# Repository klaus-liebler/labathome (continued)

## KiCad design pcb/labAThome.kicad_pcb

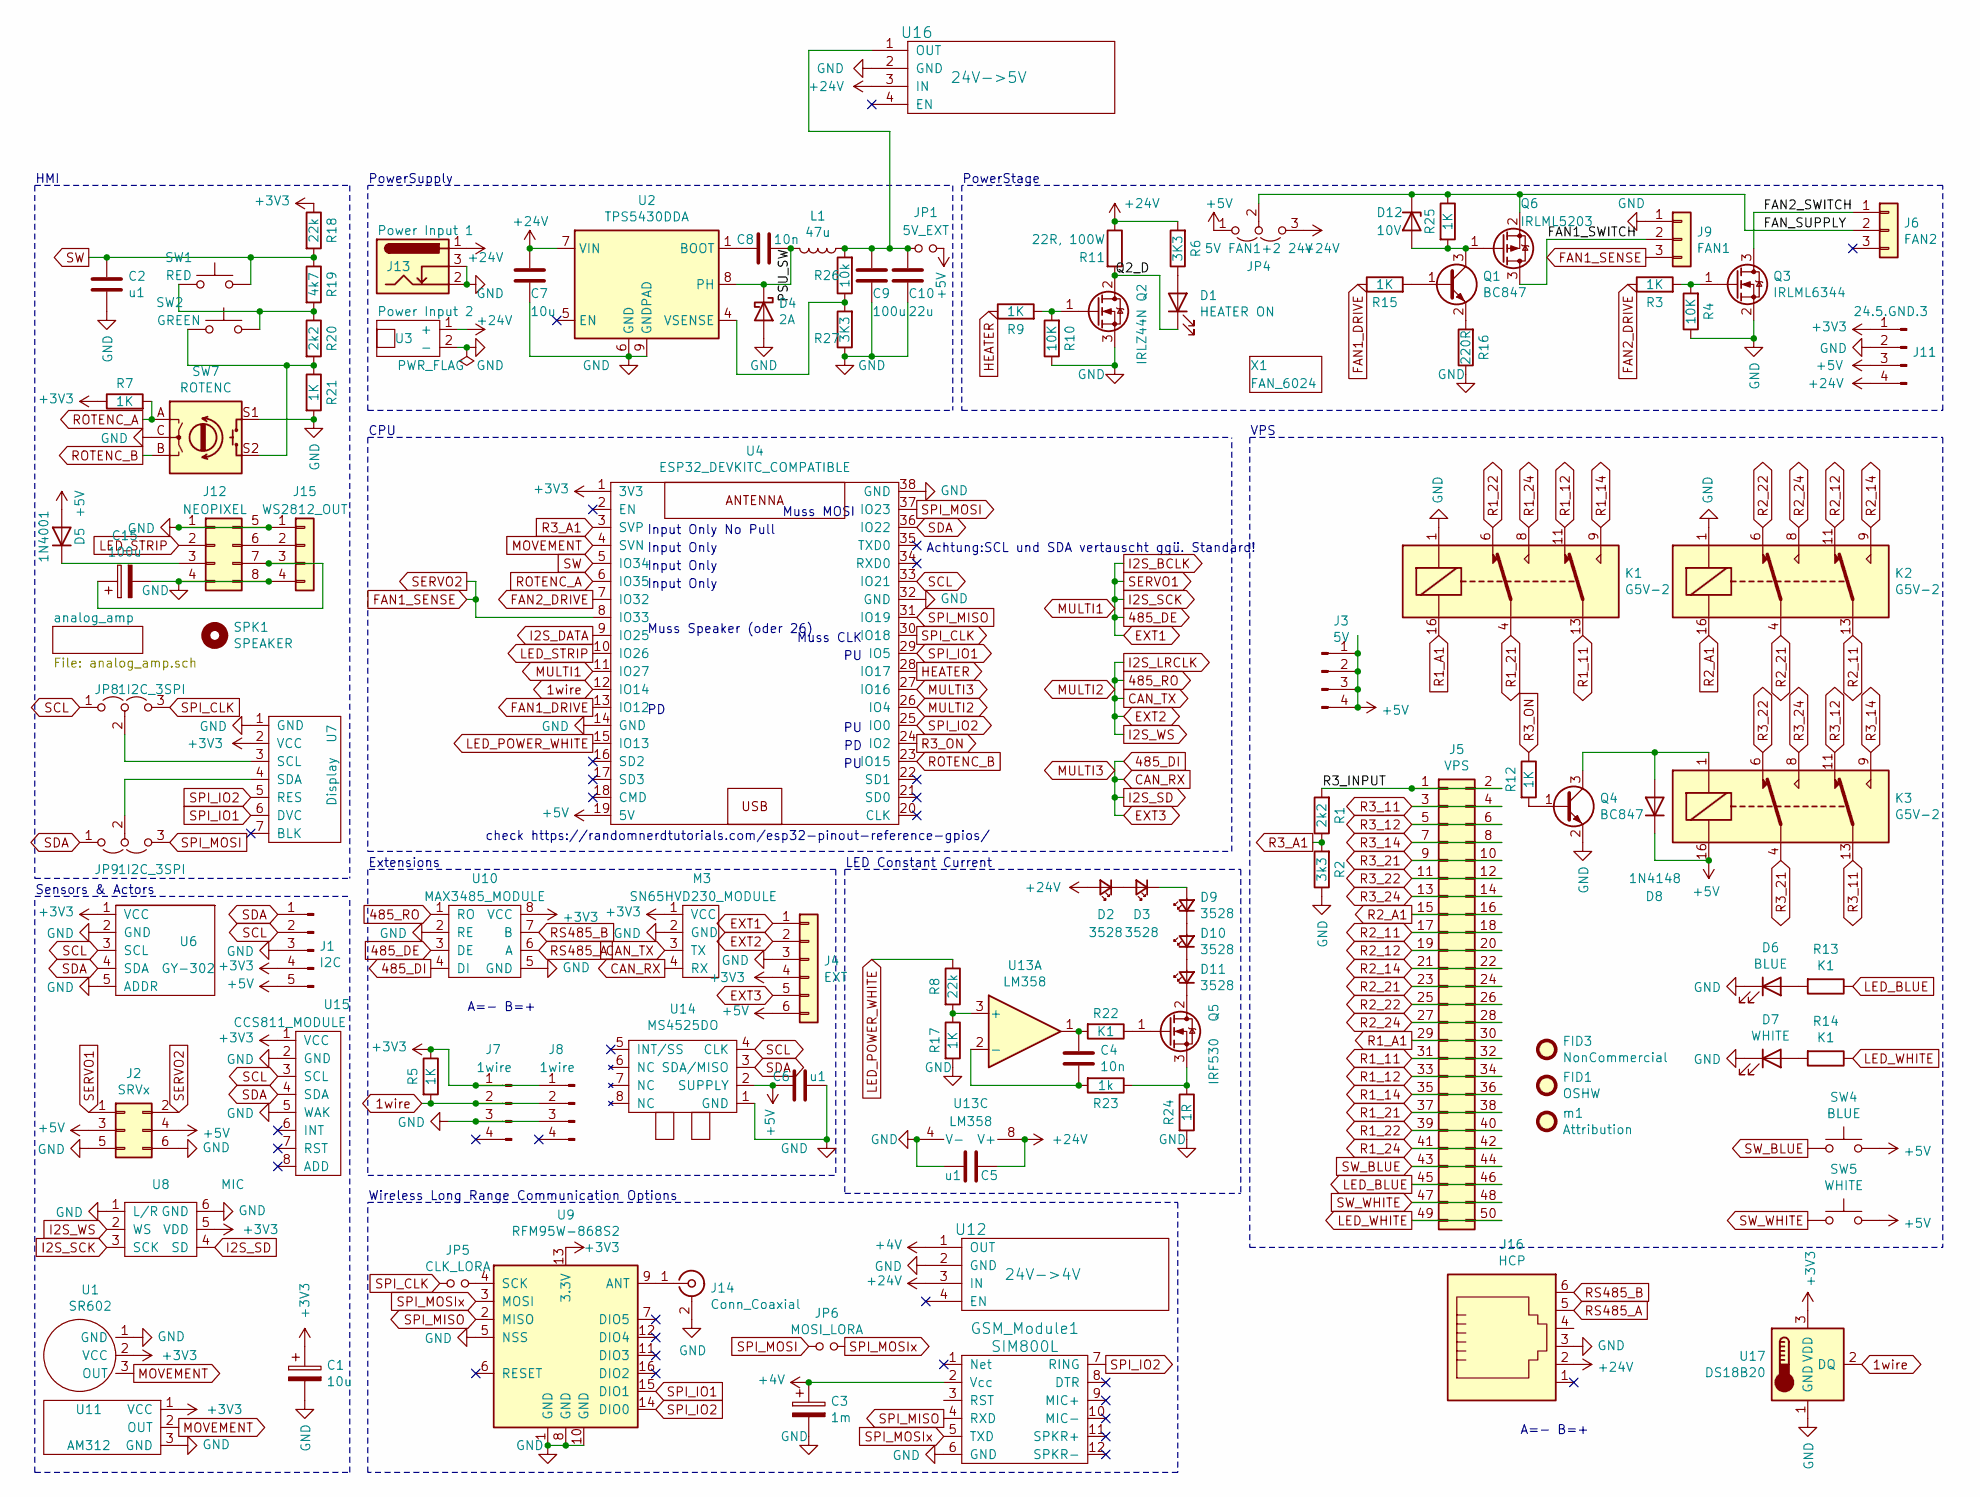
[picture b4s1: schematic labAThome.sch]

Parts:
C1: 10u; CP_EIA-3216-18_Kemet-A_Pad1.58x1.35mm_HandSolder
C2, C5, C6: u1; C_1206_3216Metric_Pad1.42x1.75mm_HandSolder
C3: 1m; CP_EIA-7360-38_Kemet-E_Pad2.25x4.25mm_HandSolder
C4: 10n; C_1206_3216Metric_Pad1.42x1.75mm_HandSolder
C7: 10u; C_1206_3216Metric_Pad1.33x1.80mm_HandSolder
C8: 10n; C_1206_3216Metric_Pad1.33x1.80mm_HandSolder
C9: 100u; C_1206_3216Metric_Pad1.33x1.80mm_HandSolder
C10: 22u; C_1206_3216Metric_Pad1.33x1.80mm_HandSolder
C15: 100u; CP_Elec_6.3x7.7_handsolder
D1: HEATER ON; LED_D5.0mm
D2, D3, D9, D10, D11: 3528; LED_PLCC_2835_Handsoldering
D4: 2A; do214aa_handsolder
D5: 1N4001; D_SMA_Handsoldering
D6: BLUE; LED_D5.0mm
D7: WHITE; LED_D5.0mm
D8: 1N4148; D_SMA_Handsoldering
D12: 10V; D_SMA_Handsoldering
FID1: OSHW; OSHW-Logo_5.7x6mm_SilkScreen
FID3: NonCommercial; Symbol_CC-Noncommercial_CopperTop_Small
GSM_Module1: SIM800L
J1: I2C; JST_XH_B5B-XH-AM_1x05_P2.50mm_Vertical
J2: SRVx; PinHeader_2x03_P2.54mm_Vertical
J3: 5V; PinHeader_1x04_P2.54mm_Vertical
J4: EXT; JST_XH_B6B-XH-A_1x06_P2.50mm_Vertical
J5: VPS; PinHeader_2x25_P2.54mm_Vertical
J6: FAN2; FanPinHeader_1x03_P2.54mm_Vertical
J7, J8: 1wire; JST_XH_B4B-XH-A_1x04_P2.50mm_Vertical
J9: FAN1; FanPinHeader_1x03_P2.54mm_Vertical
J11: 24.5.GND.3; JST_XH_B4B-XH-A_1x04_P2.50mm_Vertical
J12: NEOPIXEL; NEOPIXEL_STICK
J13: Power Input 1; BarrelJack_Horizontal
J14: Conn_Coaxial; SMA_Samtec_SMA-J-P-X-ST-EM1_EdgeMount
J15: WS2812_OUT; PinHeader_1x04_P2.54mm_Vertical
J16: HCP; WR_MJ_Modular_Jack_Vertical_Plastic_6P6C
JP1: 5V_EXT; PinHeader_1x02_P2.54mm_Vertical
JP4: 5V FAN1+2 24V; PinSocket_1x03_P2.54mm_Vertical
JP5: CLK_LORA; SolderJumper-2_P1.3mm_Open_RoundedPad1.0x1.5mm
JP6: MOSI_LORA; SolderJumper-2_P1.3mm_Open_RoundedPad1.0x1.5mm
JP8, JP9: 1I2C_3SPI; SolderJumper-3_P1.3mm_Open_RoundedPad1.0x1.5mm_NumberLabels
K1, K2, K3: G5V-2; Relay_DPDT_Omron_G5V-2
L1: 47u; Inductor_CD104_handsolder
M3: SN65HVD230_MODULE
Q1, Q4: BC847; SOT-23_Handsoldering
Q2: IRLZ44N; TO-220-3_Horizontal_TabDown
Q3: IRLML6344; SOT-23_Handsoldering
Q5: IRF530; TO-220-3_Horizontal_TabDown
Q6: IRLML5203; SOT-23_Handsoldering
R1, R20: 2k2; R_1206_3216Metric_Pad1.42x1.75mm_HandSolder
R2: 3k3; R_1206_3216Metric_Pad1.42x1.75mm_HandSolder
R3, R5, R7, R9, R12, R15, R17, R21: 1K; R_1206_3216Metric_Pad1.42x1.75mm_HandSolder
R4, R10: 10K; R_1206_3216Metric_Pad1.42x1.75mm_HandSolder
R6: 3K3; R_1206_3216Metric_Pad1.42x1.75mm_HandSolder
R8, R18: 22k; R_1206_3216Metric_Pad1.42x1.75mm_HandSolder
R11: 22R, 100W; Resistor_100W
R13, R14, R22: K1; R_1206_3216Metric_Pad1.42x1.75mm_HandSolder
R16: 220R; R_1206_3216Metric_Pad1.42x1.75mm_HandSolder
R19: 4k7; R_1206_3216Metric_Pad1.42x1.75mm_HandSolder
R23: 1k; R_1206_3216Metric_Pad1.42x1.75mm_HandSolder
R24: 1R; R_1206_3216Metric_Pad1.42x1.75mm_HandSolder
R25: 1K; R_1206_3216Metric_Pad1.30x1.75mm_HandSolder
R26: 10k; R_1206_3216Metric_Pad1.30x1.75mm_HandSolder
R27: 3K3; R_1206_3216Metric_Pad1.30x1.75mm_HandSolder
SPK1: SPEAKER; SPEAKER_2415
SW1: RED; Button_12mm_ANCHOR_CENTER
SW2: GREEN; Button_12mm_ANCHOR_CENTER
SW4: BLUE; Button_12mm_ANCHOR_CENTER
SW5: WHITE; Button_12mm_ANCHOR_CENTER
SW7: ROTENC; RotaryEncoder_Alps_EC11E-Switch_Vertical_H20mm
U1: SR602; PIR_Sensor_SR602
U2: TPS5430DDA; SOIC-8_3.9x4.9mm_Pitch1.27mm_pad_handsolder
U3: Power Input 2; PDC004_Module
U4: ESP32_DEVKITC_COMPATIBLE
U6: GY-302
U7: Display; IPS_240_240
U8: MIC; INMP441_Module
U9: RFM95W-868S2; HOPERF_RFM9XW_SMD
U10: MAX3485_MODULE
U11: AM312
U12: 24V->4V; MODULE_STEPDOWN
U13: LM358; SOIC-8_3.9x4.9mm_Pitch1.27mm_handsolder
U14: MS4525DO
U15: CCS811_MODULE
U16: 24V->5V; MODULE_STEPDOWN
U17: DS18B20; TO-92_Inline
X1: FAN_6024
m1: Attribution; Symbol_CC-Attribution_CopperTop_Small

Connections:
1wire: J7.2, J8.2, R5.2, U4.12 (IO14), U17.2 (DQ)
485_DE: J2.1, J4.1, U4.11 (IO27), U8.3 (SCK), U10.3 (DE)
485_DI: J4.5, M3.4 (RX), U4.27 (IO16), U8.4 (SD), U10.4 (DI)
485_RO: J4.2, M3.3 (TX), U4.26 (IO4), U8.2 (WS), U10.1 (RO)
+3V3: C1.1, J1.4, J4.4, J7.1, J8.1, J11.1, M3.1 (VCC), R5.1, R7.1, R18.1, U1.2 (VCC), U4.1 (3V3), U6.1 (VCC), U7.2 (VCC), U8.5 (VDD), U9.13 (3.3V), U10.8 (VCC), U11.1 (VCC), U15.1 (VCC), U17.3 (VDD); also elsewhere on the board
+4V: C3.1, GSM_Module1.2 (Vcc), U12.1 (OUT)
+5V: C6.1, D5.2 (A), D8.1 (K), J1.5, J2.3, J2.4, J3.1, J3.2, J3.3, J3.4, J4.6, J11.3, JP1.1, JP4.1 (A), K3.16, SW4.2, SW5.2, U4.19 (5V), U14.2 (SUPPLY); also elsewhere on the board
+24V: C5.1, C7.1, D2.2 (A), J11.4, J13.1, J16.2, JP4.3 (B), R6.2, R11.1, U2.7 (VIN), U3.1 (+), U12.3 (IN), U13.8 (V+), U16.3 (IN)
/FAN1_SWITCH: J9.2, Q6.3 (D)
/FAN2_SWITCH: J6.1, Q3.3 (D)
/FAN_SUPPLY: D12.1 (K), J6.2, JP4.2 (C), Q6.2 (S), R25.1
/PSU_SW: C8.2, D4.1 (K), L1.2, U2.8 (PH)
/Q2_D: D1.1 (K), Q2.2 (D), R11.2
/R3_INPUT: J5.1, J5.2, R1.2
FAN1_DRIVE: R15.1, U4.13 (IO12)
FAN1_SENSE: J2.2, J9.3, U4.8 (IO33)
FAN2_DRIVE: R3.1, U4.7 (IO32)
GND: C1.2, C2.2, C3.2, C5.2, C6.2, C7.2, C9.2, C10.2, C15.2, D4.2 (A), D6.1 (K), D7.1 (K), GSM_Module1.6 (GND), J1.3, J2.5, J2.6, J4.3, J7.3, J8.3, J9.1, J11.2, J12.1, J12.4, J12.5, J12.8, J13.2, J13.3, J14.2 (Ext), J15.1, J15.4, J16.3, K1.1, K2.1, M3.2 (GND), Q2.3 (S), Q3.2 (S), Q4.2 (E), R2.1, R4.1, R10.1, R16.1, R17.2, R21.2, R24.2, R27.1, SW7.C, SW7.S1, U1.1 (GND), U2.6 (GND), U2.9 (GNDPAD), U3.2 (-), U4.14 (GND), U4.32 (GND), U4.38 (GND), U6.2 (GND), U6.5 (ADDR), U7.1 (GND), U8.1 (L/R), U8.6 (GND), U9.1 (GND), U9.5 (NSS), U9.8 (GND), U9.10 (GND), U10.2 (RE), U10.5 (GND), U11.3 (GND), U12.2 (GND), U13.4 (V-), U14.1 (GND), U15.2 (GND), U15.5 (WAK), U16.2 (GND), U17.1 (GND); also elsewhere on the board
HEATER: R9.1, U4.28 (IO17)
I2S_DATA: U4.9 (IO25); also elsewhere on the board
LED_BLUE: J5.45, J5.46, R13.1
LED_POWER_WHITE: R8.1, U4.15 (IO13)
LED_STRIP: J12.2, U4.10 (IO26)
LED_WHITE: J5.49, J5.50, R14.1
MOVEMENT: U1.3 (OUT), U4.4 (SVN), U11.2 (OUT)
unnamed: C4.1, R22.2, U13.1
unnamed: C4.2, R23.2, U13.2 (-)
unnamed: C8.1, U2.1 (BOOT)
unnamed: C9.1, C10.1, JP1.2, L1.1, R26.2, U16.1 (OUT)
unnamed: C15.1, J12.7, J15.3
unnamed: D1.2 (A), R6.1
unnamed: D2.1 (K), D3.2 (A)
unnamed: D3.1 (K), D9.2 (A)
unnamed: D5.1 (K), J12.3
unnamed: D6.2 (A), R13.2
unnamed: D7.2 (A), R14.2
unnamed: D8.2 (A), K3.1, Q4.3 (C)
unnamed: D10.1 (K), D11.2 (A)
unnamed: D9.1 (K), D10.2 (A)
unnamed: D11.1 (K), Q5.2 (D)
unnamed: D12.2 (A), Q1.3 (C), Q6.1 (G), R25.2
unnamed: J12.6, J15.2
unnamed: J14.1 (In), U9.9 (ANT)
unnamed: JP5.2, U9.4 (SCK)
unnamed: JP8.2 (C), U7.3 (SCL)
unnamed: JP9.2 (C), U7.4 (SDA)
unnamed: Q1.1 (B), R15.2
unnamed: Q1.2 (E), R16.2
unnamed: Q2.1 (G), R9.2, R10.2
unnamed: Q3.1 (G), R3.2, R4.2
unnamed: Q4.1 (B), R12.2
unnamed: Q5.1 (G), R22.1
unnamed: Q5.3 (S), R23.1, R24.1
unnamed: R8.2, R17.1, U13.3 (+)
unnamed: R19.2, R20.1, SW1.2, SW2.2
unnamed: R20.2, R21.1, SW2.1, SW7.S2
unnamed: R26.1, R27.2, U2.4 (VSENSE)
R1_11: J5.31, J5.32, K1.13
R1_12: J5.33, J5.34, K1.11
R1_14: J5.35, J5.36, K1.9
R1_21: J5.37, J5.38, K1.4
R1_22: J5.39, J5.40, K1.6
R1_24: J5.41, J5.42, K1.8
R1_A1: J5.29, J5.30, K1.16
R2_11: J5.17, J5.18, K2.13
R2_12: J5.19, J5.20, K2.11
R2_14: J5.21, J5.22, K2.9
R2_21: J5.23, J5.24, K2.4
R2_22: J5.25, J5.26, K2.6
R2_24: J5.27, J5.28, K2.8
R2_A1: J5.15, J5.16, K2.16
R3_11: J5.3, J5.4, K3.13
R3_12: J5.5, J5.6, K3.11
R3_14: J5.7, J5.8, K3.9
R3_21: J5.9, J5.10, K3.4
R3_22: J5.11, J5.12, K3.6
R3_24: J5.13, J5.14, K3.8
R3_A1: R1.1, R2.2, U4.3 (SVP)
R3_ON: R12.1, U4.24 (IO2)
ROTENC_A: R7.2, SW7.A, U4.6 (IO35)
ROTENC_B: SW7.B, U4.23 (IO15)
RS485_A: J16.5, U10.6 (A)
RS485_B: J16.6, U10.7 (B)
SCL: J1.2, JP8.1 (A), U4.33 (IO21), U6.3 (SCL), U14.4 (CLK), U15.3 (SCL)
SDA: J1.1, JP9.1 (A), U4.36 (IO22), U6.4 (SDA), U14.3 (SDA/MISO), U15.4 (SDA)
SPI_CLK: JP5.1, JP8.3 (B), U4.30 (IO18)
SPI_IO1: U4.29 (IO5), U7.6 (DVC), U9.15 (DIO1)
SPI_IO2: GSM_Module1.7 (RING), U4.25 (IO0), U7.5 (RES), U9.14 (DIO0)
SPI_MISO: GSM_Module1.4 (RXD), U4.31 (IO19), U9.2 (MISO)
SPI_MOSI: JP6.1, JP9.3 (B), U4.37 (IO23)
SPI_MOSIx: GSM_Module1.5 (TXD), JP6.2, U9.3 (MOSI)
SW: C2.1, R18.2, R19.1, SW1.1, U4.5 (IO34)
SW_BLUE: J5.43, J5.44, SW4.1
SW_WHITE: J5.47, J5.48, SW5.1

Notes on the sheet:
PowerStage
HMI
VPS
Sensors & Actors
CPU
check https://randomnerdtutorials.com/esp32-pinout-reference-gpios/
Muss CLK
Input Only No Pull
Input Only
Muss MOSI
Muss Speaker (oder 26)
Achtung:SCL und SDA vertauscht ggü. Standard!
Extensions
Wireless Long Range Communication Options
LED Constant Current
PowerSupply
A=- B=+

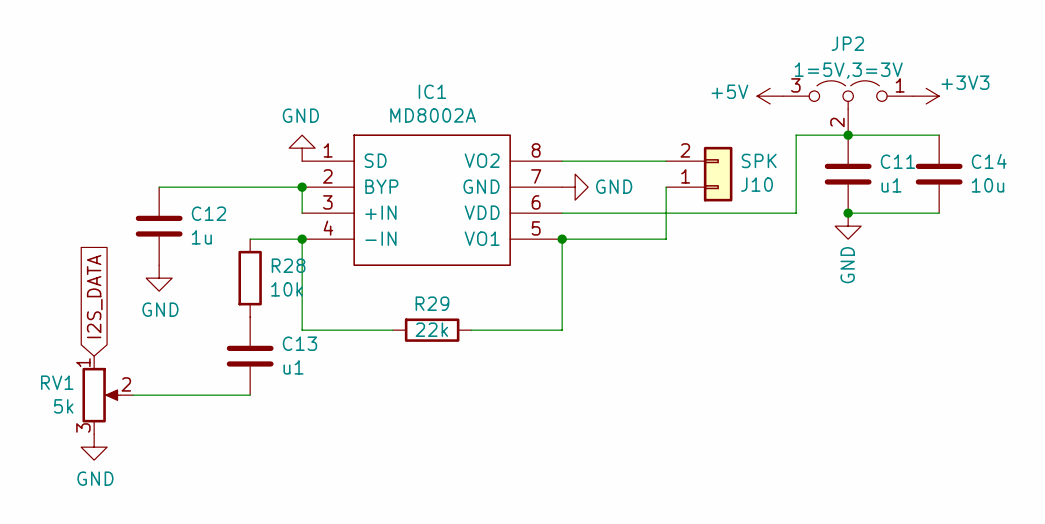
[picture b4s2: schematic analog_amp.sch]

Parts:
C11, C13: u1; C_1206_3216Metric_Pad1.33x1.80mm_HandSolder
C12: 1u; C_1206_3216Metric_Pad1.33x1.80mm_HandSolder
C14: 10u; C_1206_3216Metric_Pad1.33x1.80mm_HandSolder
IC1: MD8002A; SOIC-8_3.9x4.9mm_Pitch1.27mm_handsolder; Manufacturer_Part_Number MD8002A
J10: SPK; PinHeader_1x02_P2.54mm_Vertical
JP2: 1=5V,3=3V; SolderJumper-3_P1.3mm_Open_RoundedPad1.0x1.5mm_NumberLabels
R28: 10k; R_1206_3216Metric_Pad1.30x1.75mm_HandSolder
R29: 22k; R_1206_3216Metric_Pad1.30x1.75mm_HandSolder
RV1: 5k; Potentiometer_Alps_RK09K_Single_Vertical

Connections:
+3V3: JP2.1 (A); also elsewhere on the board
+5V: JP2.3 (B); also elsewhere on the board
GND: C11.2, C12.2, C14.2, IC1.1 (SD), IC1.7 (GND), RV1.3; also elsewhere on the board
I2S_DATA: RV1.1; also elsewhere on the board
unnamed: C11.1, C14.1, IC1.6 (VDD), JP2.2 (C)
unnamed: C12.1, IC1.2 (BYP), IC1.3 (+IN)
unnamed: C13.1, R28.2
unnamed: C13.2, RV1.2
unnamed: IC1.4 (-IN), R28.1, R29.2
unnamed: IC1.5 (VO1), J10.1, R29.1
unnamed: IC1.8 (VO2), J10.2

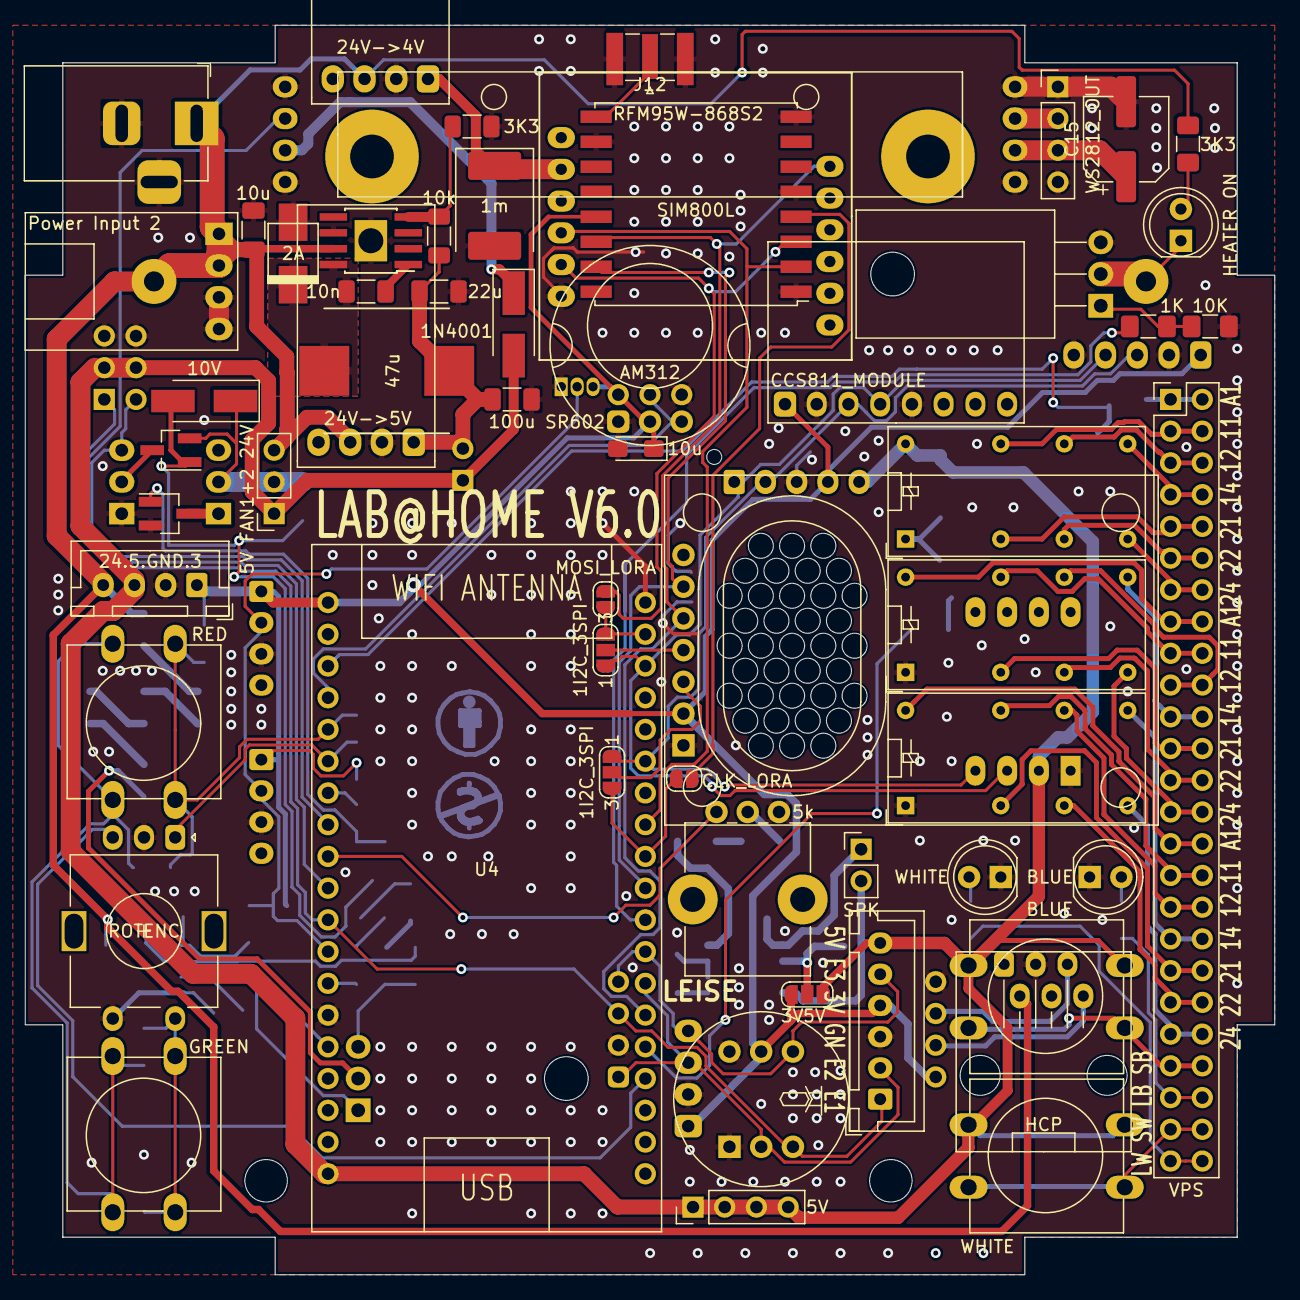
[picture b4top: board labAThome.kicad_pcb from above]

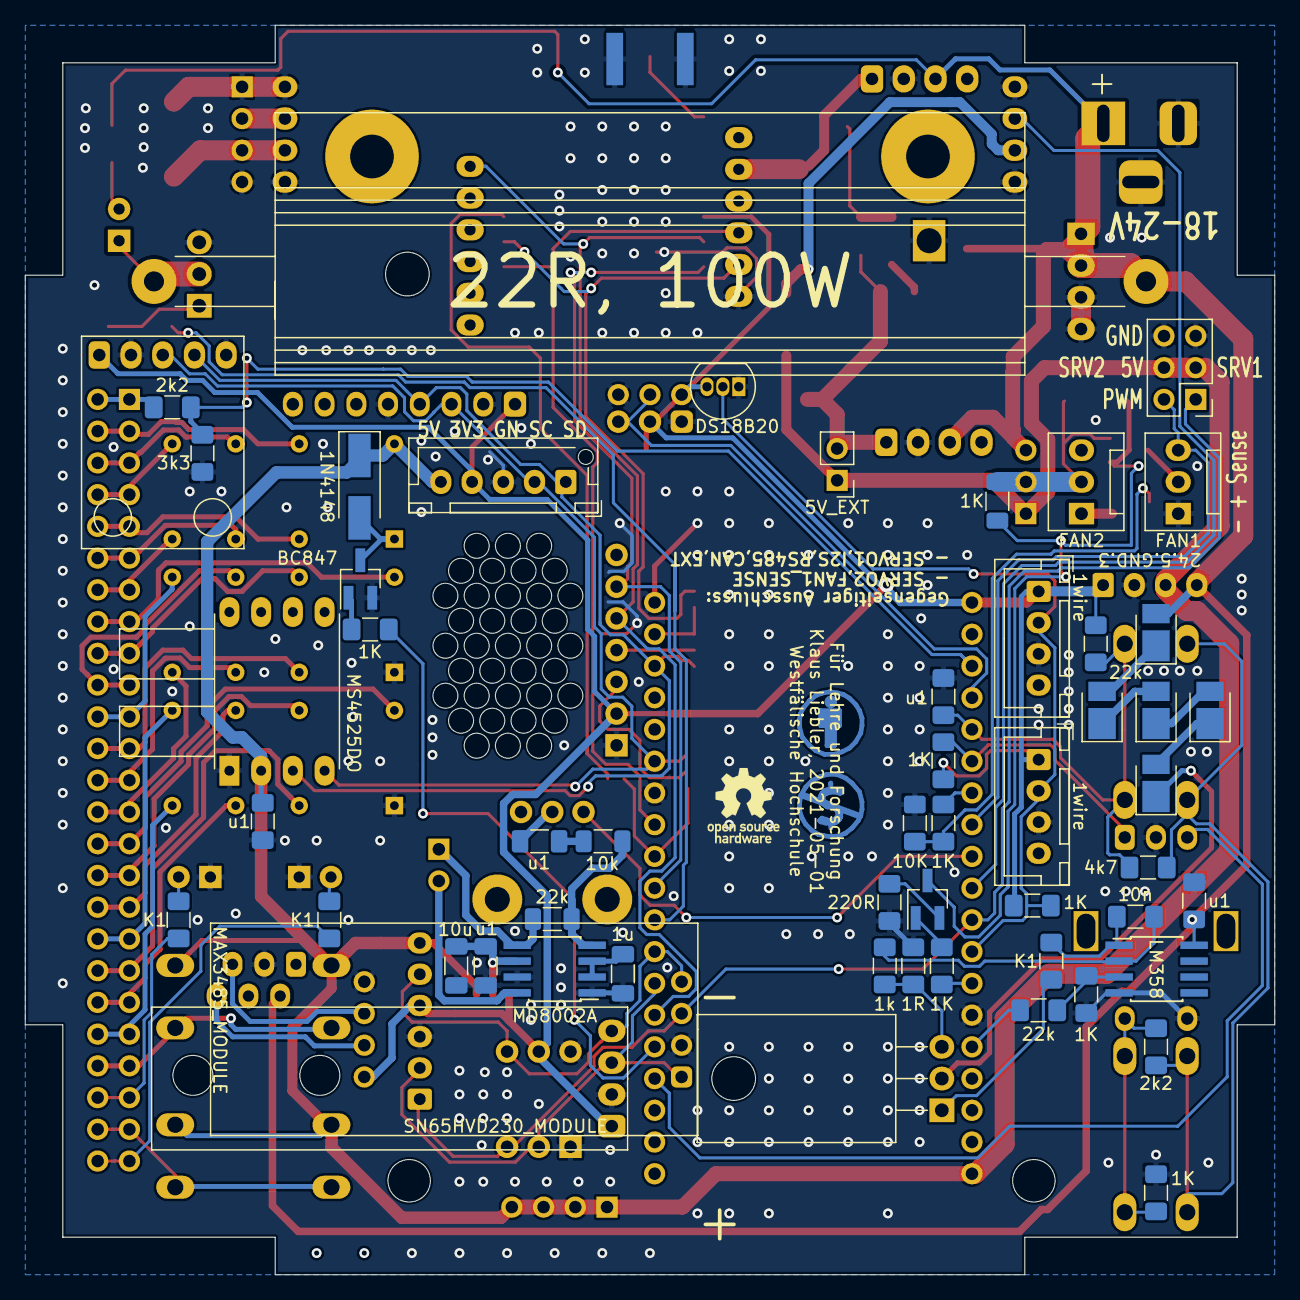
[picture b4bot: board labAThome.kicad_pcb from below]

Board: 2 copper layers, 100.0 x 100.0 mm, 119 parts (59 on the bottom side), 101 nets.

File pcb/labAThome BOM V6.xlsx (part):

Reference | Value | Footprint | Datasheet | Option | Description | Height | Manufacturer_Name | Manufacturer_Part_Number
C1 | 10u | Capacitor_Tantalum_SMD:CP_EIA-3216-18_Kemet-A_Pad1.58x1.35mm_HandSolder | ~
C11 | u1 | Capacitor_SMD:C_1206_3216Metric_Pad1.33x1.80mm_HandSolder | ~ | Sound only
Q2 | IRLZ44N | Package_TO_SOT_THT:TO-220-3_Horizontal_TabDown | ~ | Heater only
R11 | 22R, 100W | smopla:Resistor_100W | ~ | Heater only
K1 | G5V-2 | Relay_THT:Relay_DPDT_Omron_G5V-2 | http://omronfs.omron.com/en_US/ecb/products/pdf/en-g5v_2.pdf | VPS only
K3 | G5V-2 | Relay_THT:Relay_DPDT_Omron_G5V-2 | http://omronfs.omron.com/en_US/ecb/products/pdf/en-g5v_2.pdf | VPS only
D6 | BLUE | LED_THT:LED_D5.0mm | ~ | VPS only
D7 | WHITE | LED_THT:LED_D5.0mm | ~ | VPS only
SW5 | WHITE | liebler_MECH:Button_12mm_ANCHOR_CENTER | ~ | VPS only
SW4 | BLUE | liebler_MECH:Button_12mm_ANCHOR_CENTER | ~ | VPS only
C12 | 1u | Capacitor_SMD:C_1206_3216Metric_Pad1.33x1.80mm_HandSolder | ~ | Sound only
R14 | K1 | Resistor_SMD:R_1206_3216Metric_Pad1.42x1.75mm_HandSolder | ~ | VPS only
R13 | K1 | Resistor_SMD:R_1206_3216Metric_Pad1.42x1.75mm_HandSolder | ~ | VPS only
K2 | G5V-2 | Relay_THT:Relay_DPDT_Omron_G5V-2 | http://omronfs.omron.com/en_US/ecb/products/pdf/en-g5v_2.pdf | VPS only
R10 | 10K | Resistor_SMD:R_1206_3216Metric_Pad1.42x1.75mm_HandSolder | ~ | Heater only
R9 | 1K | Resistor_SMD:R_1206_3216Metric_Pad1.42x1.75mm_HandSolder | ~ | Heater only
J9 | FAN1 | Connector:FanPinHeader_1x03_P2.54mm_Vertical | ~ | Heater only
R15 | 1K | Resistor_SMD:R_1206_3216Metric_Pad1.42x1.75mm_HandSolder | ~ | Heater only
C13 | u1 | Capacitor_SMD:C_1206_3216Metric_Pad1.33x1.80mm_HandSolder | ~ | Sound only
C14 | 10u | Capacitor_SMD:C_1206_3216Metric_Pad1.33x1.80mm_HandSolder | ~ | Sound only
D8 | 1N4148 | Diode_SMD:D_SMA_Handsoldering | https://assets.nexperia.com/documents/data-sheet/1N4148_1N4448.pdf | VPS only
R12 | 1K | Resistor_SMD:R_1206_3216Metric_Pad1.42x1.75mm_HandSolder | ~ | VPS only
C15 | 100u | liebler_PASSIVES:CP_Elec_6.3x7.7_handsolder | ~
R1 | 2k2 | Resistor_SMD:R_1206_3216Metric_Pad1.42x1.75mm_HandSolder | ~ | VPS only
R2 | 3k3 | Resistor_SMD:R_1206_3216Metric_Pad1.42x1.75mm_HandSolder | ~ | VPS only
U8 | MIC | smopla:INMP441_Module |  | Microphone only
C2 | u1 | Capacitor_SMD:C_1206_3216Metric_Pad1.42x1.75mm_HandSolder | ~
J5 | VPS | Connector_PinHeader_2.54mm:PinHeader_2x25_P2.54mm_Vertical | ~ | VPS only
C4 | 10n | Capacitor_SMD:C_1206_3216Metric_Pad1.42x1.75mm_HandSolder | ~ | PowerLED only
C5 | u1 | Capacitor_SMD:C_1206_3216Metric_Pad1.42x1.75mm_HandSolder | ~ | PowerLED only
D10 | 3528 | LED_SMD:LED_PLCC_2835_Handsoldering | ~ | PowerLED only
J3 | 5V | Connector_PinHeader_2.54mm:PinHeader_1x04_P2.54mm_Vertical | ~ | VPS only
X1 | FAN_6024 | smopla:FAN_6024 |  | Heater only
JP4 | 5V FAN1+2 24V | Connector_PinSocket_2.54mm:PinSocket_1x03_P2.54mm_Vertical | ~ | Heater only
D11 | 3528 | LED_SMD:LED_PLCC_2835_Handsoldering | ~ | PowerLED only
D2 | 3528 | LED_SMD:LED_PLCC_2835_Handsoldering | ~ | PowerLED only
D3 | 3528 | LED_SMD:LED_PLCC_2835_Handsoldering | ~ | PowerLED only
D5 | 1N4001 | Diode_SMD:D_SMA_Handsoldering | http://www.vishay.com/docs/88503/1n4001.pdf
U11 | AM312 | smopla:AM312 |  | Alternative PIR only
D9 | 3528 | LED_SMD:LED_PLCC_2835_Handsoldering | ~ | PowerLED only
FID1 | OSHW | Symbol:OSHW-Logo_5.7x6mm_SilkScreen | ~
FID3 | NonCommercial | Symbol:Symbol_CC-Noncommercial_CopperTop_Small | ~
IC1 | MD8002A | sensact:SOIC-8_3.9x4.9mm_Pitch1.27mm_handsolder | https://www.sunrom.com/get/408862 |  | Audio Amplifier, SOP8 | 175 | Sunrom | MD8002A
J1 | I2C | Connector_JST:JST_XH_B5B-XH-AM_1x05_P2.50mm_Vertical | ~
J10 | SPK | Connector_PinHeader_2.54mm:PinHeader_1x02_P2.54mm_Vertical | ~
J11 | 24.5.GND.3 | Connector_JST:JST_XH_B4B-XH-A_1x04_P2.50mm_Vertical | ~
J12 | NEOPIXEL | liebler_MODULES:NEOPIXEL_STICK | ~
J13 | Power Input 1 | Connector_BarrelJack:BarrelJack_Horizontal | ~
J14 | Conn_Coaxial | Connector_Coaxial:SMA_Samtec_SMA-J-P-X-ST-EM1_EdgeMount | ~
J15 | WS2812_OUT | Connector_PinHeader_2.54mm:PinHeader_1x04_P2.54mm_Vertical | ~
U9 | RFM95W-868S2 | RF_Module:HOPERF_RFM9XW_SMD | https://www.hoperf.com/data/upload/portal/20181127/5bfcbea20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 | LoRaWan only
J2 | SRVx | Connector_PinHeader_2.54mm:PinHeader_2x03_P2.54mm_Vertical | ~
J4 | EXT | Connector_JST:JST_XH_B6B-XH-A_1x06_P2.50mm_Vertical | ~
J6 | FAN2 | Connector:FanPinHeader_1x03_P2.54mm_Vertical | ~
J7 | 1wire | Connector_JST:JST_XH_B4B-XH-A_1x04_P2.50mm_Vertical | ~
J8 | 1wire | Connector_JST:JST_XH_B4B-XH-A_1x04_P2.50mm_Vertical | ~
JP1 | 5V_EXT | Connector_PinHeader_2.54mm:PinHeader_1x02_P2.54mm_Vertical | ~
Q4 | BC847 | Package_TO_SOT_SMD:SOT-23_Handsoldering | http://www.infineon.com/dgdl/Infineon-BC847SERIES_BC848SERIE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 | VPS only
JP2 | 1=5V,3=3V | Jumper:SolderJumper-3_P1.3mm_Open_RoundedPad1.0x1.5mm_NumberLabels | ~
JP5 | CLK_LORA | Jumper:SolderJumper-2_P1.3mm_Open_RoundedPad1.0x1.5mm | ~
JP6 | MOSI_LORA | Jumper:SolderJumper-2_P1.3mm_Open_RoundedPad1.0x1.5mm | ~
JP8 | 1I2C_3SPI | Jumper:SolderJumper-3_P1.3mm_Open_RoundedPad1.0x1.5mm_NumberLabels | ~
JP9 | 1I2C_3SPI | Jumper:SolderJumper-3_P1.3mm_Open_RoundedPad1.0x1.5mm_NumberLabels | ~
m1 | Attribution | Symbol:Symbol_CC-Attribution_CopperTop_Small | ~
R6 | 3K3 | Resistor_SMD:R_1206_3216Metric_Pad1.42x1.75mm_HandSolder | ~ | Heater only
D1 | HEATER ON | LED_THT:LED_D5.0mm | ~ | Heater only
M3 | SN65HVD230_MODULE | smopla:SN65HVD230_MODULE
U12 | 24V->4V | sensact:MODULE_STEPDOWN |  | LoRaWan only
GSM_Module1 | SIM800L | smopla:SIM800L |  | LoRaWan only
C3 | 1m | Capacitor_Tantalum_SMD:CP_EIA-7360-38_Kemet-E_Pad2.25x4.25mm_HandSolder | ~ | LoRaOnly
Q3 | IRLML6344 | Package_TO_SOT_SMD:SOT-23_Handsoldering | https://www.infineon.com/dgdl/irlml0030pbf.pdf?fileId=5546d4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
Q5 | IRF530 | Package_TO_SOT_THT:TO-220-3_Horizontal_TabDown | ~ | PowerLED only
R17 | 1K | Resistor_SMD:R_1206_3216Metric_Pad1.42x1.75mm_HandSolder | ~ | PowerLED only
R18 | 22k | Resistor_SMD:R_1206_3216Metric_Pad1.42x1.75mm_HandSolder | ~
R19 | 4k7 | Resistor_SMD:R_1206_3216Metric_Pad1.42x1.75mm_HandSolder | ~
R20 | 2k2 | Resistor_SMD:R_1206_3216Metric_Pad1.42x1.75mm_HandSolder | ~
R21 | 1K | Resistor_SMD:R_1206_3216Metric_Pad1.42x1.75mm_HandSolder | ~
R22 | K1 | Resistor_SMD:R_1206_3216Metric_Pad1.42x1.75mm_HandSolder | ~ | PowerLED only
R23 | 1k | Resistor_SMD:R_1206_3216Metric_Pad1.42x1.75mm_HandSolder | ~ | PowerLED only
R24 | 1R | Resistor_SMD:R_1206_3216Metric_Pad1.42x1.75mm_HandSolder | ~ | PowerLED only
R28 | 10k | Resistor_SMD:R_1206_3216Metric_Pad1.30x1.75mm_HandSolder | ~ | Sound only
R29 | 22k | Resistor_SMD:R_1206_3216Metric_Pad1.30x1.75mm_HandSolder | ~ | Sound only
R3 | 1K | Resistor_SMD:R_1206_3216Metric_Pad1.42x1.75mm_HandSolder | ~
R4 | 10K | Resistor_SMD:R_1206_3216Metric_Pad1.42x1.75mm_HandSolder | ~
R5 | 1K | Resistor_SMD:R_1206_3216Metric_Pad1.42x1.75mm_HandSolder | ~
R7 | 1K | Resistor_SMD:R_1206_3216Metric_Pad1.42x1.75mm_HandSolder | ~
R8 | 22k | Resistor_SMD:R_1206_3216Metric_Pad1.42x1.75mm_HandSolder | ~ | PowerLED only
C6 | u1 | Capacitor_SMD:C_1206_3216Metric_Pad1.42x1.75mm_HandSolder | ~ | PressureSensor only
Q1 | BC847 | Package_TO_SOT_SMD:SOT-23_Handsoldering | http://www.infineon.com/dgdl/Infineon-BC847SERIES_BC848SERIE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 | Heater only
Q6 | IRLML5203 | Package_TO_SOT_SMD:SOT-23_Handsoldering | https://www.infineon.com/dgdl/irlml5203pbf.pdf?fileId=5546d4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 | Heater only
RV1 | 5k | Potentiometer_THT:Potentiometer_Alps_RK09K_Single_Vertical | ~ | Sound only
R25 | 1K | Resistor_SMD:R_1206_3216Metric_Pad1.30x1.75mm_HandSolder | ~ | Heater only
R16 | 220R | Resistor_SMD:R_1206_3216Metric_Pad1.42x1.75mm_HandSolder | ~ | Heater only
D12 | 10V | Diode_SMD:D_SMA_Handsoldering | ~ | Heater only
U2 | TPS5430DDA | sensact:SOIC-8_3.9x4.9mm_Pitch1.27mm_pad_handsolder | http://www.ti.com/lit/ds/symlink/tps5430.pdf | DiscretePSU only
C7 | 10u | Capacitor_SMD:C_1206_3216Metric_Pad1.33x1.80mm_HandSolder | ~ | DiscretePSU only
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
